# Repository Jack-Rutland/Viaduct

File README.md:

# viaduct

An MCP server that lets Claude do PCB work in [KiCad](https://kicad.org): inspect boards,
place footprints (collision- and outline-aware), lay manual copper, measure ratsnest
length, run ERC/DRC, render images for visual review, and export fabrication outputs.

No KiCad Python bindings required — viaduct parses `.kicad_pcb` / `.kicad_sch` files with
its own s-expression parser and shells out to `kicad-cli` for checks, exports, and renders.
Verified against KiCad 10.0 file output (KiCad 8/9 net tables are also understood).

## Install

Requirements: Python 3.10+, KiCad 8 or newer (developed and tested against KiCad 10.0).

```sh
git clone <this-repo> viaduct && cd viaduct
pip install .
```

Register with Claude Code:

```sh
claude mcp add viaduct -- viaduct
```

`kicad-cli` is found automatically (on macOS inside
`/Applications/KiCad/KiCad.app/Contents/MacOS/`). If yours lives elsewhere:

```sh
claude mcp add viaduct -e VIADUCT_KICAD_CLI=/path/to/kicad-cli -- viaduct
```

Sanity check: ask Claude to run the `kicad_version` tool.

## Tools

| Tool | What it does |
|---|---|
| `kicad_version` | Locate kicad-cli and report its version (install sanity check) |
| `run_drc` | Design Rules Check via kicad-cli; clean summary with severity, description, position (mm) |
| `run_erc` | Electrical Rules Check on a schematic; same summary format |
| `board_info` | Layers, thickness, outline bounding box, element counts |
| `list_footprints` | Every footprint: reference, value, position, rotation, layer |
| `list_nets` | All net names |
| `connectivity` | Per footprint: each pad's net name and absolute position (mm) |
| `courtyards` | Per footprint: courtyard bounding box in board coordinates (mm) |
| `ratsnest` | Unrouted connections as airwires (from-pad, to-pad, length mm) — the placement metric |
| `design_rules` | Clearance / track width / via rules from board setup + `.kicad_pro` net classes |
| `check_collisions` | Footprint pairs whose courtyards overlap (or sit closer than a clearance), via SAT |
| `pad_position` | Absolute position, net, and size of a single pad (e.g. `U1`, `28`) |
| `net_endpoints` | Every pad on a net with positions + how many track clusters remain |
| `measure_placement_quality` | Ratsnest length, airwire/collision counts, area use — components, not a blended score |
| `footprint_info` | Dimensions, pad count, courtyard of a library footprint, *without* placing it |
| `move_footprint` | Move/rotate one footprint (pad angles handled), with backup; can reject collisions |
| `move_footprints` | Batch move — one backup, one save; reports collisions, optional reject-on-collision |
| `nearest_free_position` | Closest spot to a pin where a footprint's courtyard clears everything, on-board and outside keep-outs (no move) |
| `auto_place_decoupling` | Seat decoupling caps against the IC pin each shares a net with, on-board and clear of keep-outs |
| `find_clear_region` | Find an empty area of a given size on a layer, nearest a pin or the board centre |
| `set_board_outline_rect` | Replace the Edge.Cuts outline with a rectangle |
| `add_rule_area` | Add a keep-out rule area over a polygon |
| `add_filled_zone` | Add a copper-pour zone outline on a net (KiCad computes the fill on open) |
| `route_trace` | Draw a copper track for a net along a polyline you supply |
| `place_via` | Add a via on a net joining two layers |
| `delete_track` | Delete tracks/vias matching a net/layer/uuid filter (undo a route) |
| `measure_track_length` | Routed copper length on a net + via count (the routed counterpart to `ratsnest`) |
| `generate_spiral_coil` | Lay an Archimedean spiral (e.g. NFC antenna) as track segments |
| `apply_netclass` | Assign a net to an existing netclass in the `.kicad_pro` |
| `restore_backup` | Restore a file from the `.bak` written before the last edit |
| `backup_create` | Snapshot a file under a chosen name (a checkpoint before a risky change) |
| `backup_list` / `backup_restore_to` | List the rolling history + named snapshots and restore any entry |
| `list_symbols` | Schematic symbols: reference, value, lib_id, footprint, position |
| `list_labels` | Local/global/hierarchical net labels |
| `set_symbol_property` | Set Value, Footprint, MPN, … on a symbol |
| `export_gerbers` | Fabrication Gerbers + drill files |
| `export_bom` | CSV bill of materials |
| `export_step` | 3D STEP model |
| `export_netlist` | Netlist (kicadsexpr, kicadxml, spice, …) |
| `render_board_svg` | Selected layers to a single SVG (board area only) |
| `render_board_png` | PNG render returned as an image, so the agent can *see* the board |

All coordinates are millimetres in KiCad's board frame (X right, **Y down**); rotations are
degrees counter-clockwise.

## The placement loop

viaduct is built around an iterate-until-clean placement workflow:

1. **Understand** — `board_info`, `design_rules`, `list_footprints`, `connectivity`,
   `ratsnest`: what's on the board, what connects to what, how bad is it now.
2. **Place** — `move_footprints` in batches (decoupling caps next to their IC pins,
   connectors on edges, group by function). `move_footprints` reports any courtyard
   collisions it creates and can `reject_on_collision`; `nearest_free_position` and
   `auto_place_decoupling` place parts against a pin without overlap in the first place.
3. **Look** — `render_board_png`: the model visually inspects its own placement.
4. **Measure** — `measure_placement_quality` / `ratsnest`: airwire length and collision
   count should drop. `check_collisions` lists any remaining courtyard overlaps directly.
5. **Verify** — `run_drc`: fix courtyard overlaps and clearance violations.
6. Repeat 2–5 until DRC is clean and the render looks tidy.

## Important: close the board in KiCad first

Editing tools check for KiCad's lockfile (`~<name>.kicad_pcb.lck`) and **refuse to edit a
file that is open in KiCad** — KiCad would silently overwrite the changes on its next save.
Close the board (or schematic) in KiCad before asking Claude to edit it, then reopen to
review. Every edit writes a `.bak` next to the file first; `restore_backup` undoes the
last edit. (If KiCad crashed and left a stale lockfile, delete it manually.)

Renders, exports, and all read-only tools are safe to use while KiCad is open.

## Example prompts

> Place all decoupling caps within 2mm of their IC pins on mainboard.kicad_pcb, then show me a render.

> Run DRC on the board and fix all courtyard overlaps by nudging the offending parts apart.

> What's the total airwire length on revB.kicad_pcb, and which three nets contribute the most?

> Set the footprint of every 100n cap in power.kicad_sch to Capacitor_SMD:C_0402_1005Metric and re-export the BOM.

## Layout session prompt

Copy-paste this to start a full placement session:

---
Lay out the board at <path/to/board.kicad_pcb>. Process:
1. Read board_info, design_rules, list_footprints, connectivity, and
   ratsnest to understand the design before moving anything.
2. Plan placement: group by function, decoupling caps within 2mm of the
   pins they serve, connectors on board edges, crystals close to their
   MCU with short paths, minimize total airwire length and crossings.
3. Apply with move_footprints in batches.
4. render_board_png and visually inspect; check ratsnest length again.
5. run_drc; fix every courtyard overlap and clearance violation.
6. Repeat 3-5 until DRC is clean and the render looks tidy, then report
   total airwire length before vs after and remaining concerns.
Never edit while the board is open in KiCad.
---

To route after placing, plan each net's path yourself (from `connectivity` and
`design_rules` clearances) and lay it with `route_trace` / `place_via`, then run `run_drc`
to catch shorts and clearance violations — there is no autorouter. `delete_track` undoes a
route; `measure_track_length` reports routed length per net.

## Development

```sh
python3 tests/test_viaduct.py
```

The test script verifies viaduct against the real KiCad installation: it round-trips a
KiCad-saved board through the parser and confirms `kicad-cli` still accepts it, checks
computed pad positions against KiCad's own IPC-D-356 export (including rotated
footprints), and exercises every tool. The fixture project in `tests/test_project/` was
saved by KiCad 10.0.3.

## License

MIT

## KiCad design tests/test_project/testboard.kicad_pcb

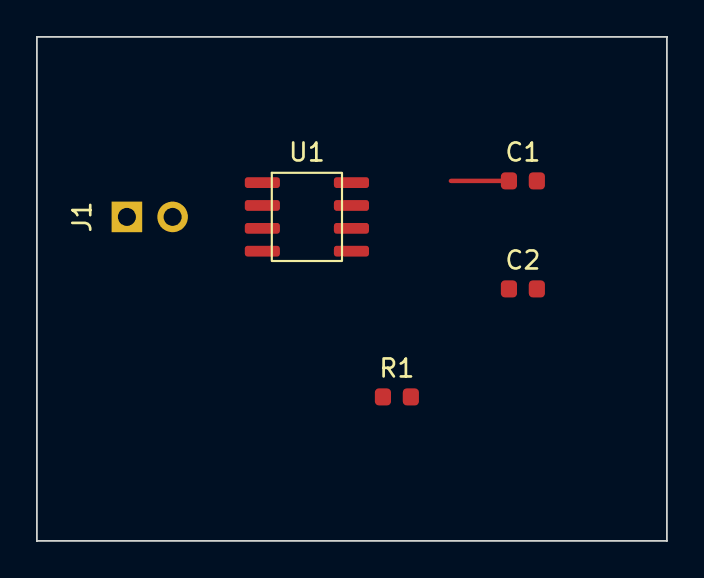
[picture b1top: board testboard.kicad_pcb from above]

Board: 2 copper layers, 35.0 x 28.0 mm, 5 parts (0 on the bottom side), 4 nets.

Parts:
C1: 100n; C_0603_1608Metric
C2: 1u; C_0603_1608Metric
J1: PWR; PinHeader_1x02_P2.54mm_Vertical
R1: 10k; R_0603_1608Metric
U1: MCP6002; SOIC-8_3.9x4.9mm_P1.27mm

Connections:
GND: C1.2, C2.2, J1.2, U1.4
IN: R1.1, U1.2
OUT: C2.1, R1.2, U1.1
VCC: C1.1, J1.1, U1.8

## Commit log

2026-06-13 Init commit
2026-06-13 major enhancement
2026-06-13 add more tools
